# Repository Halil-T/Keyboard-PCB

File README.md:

# Keyboard-PCB
First Custom keyboard PCB

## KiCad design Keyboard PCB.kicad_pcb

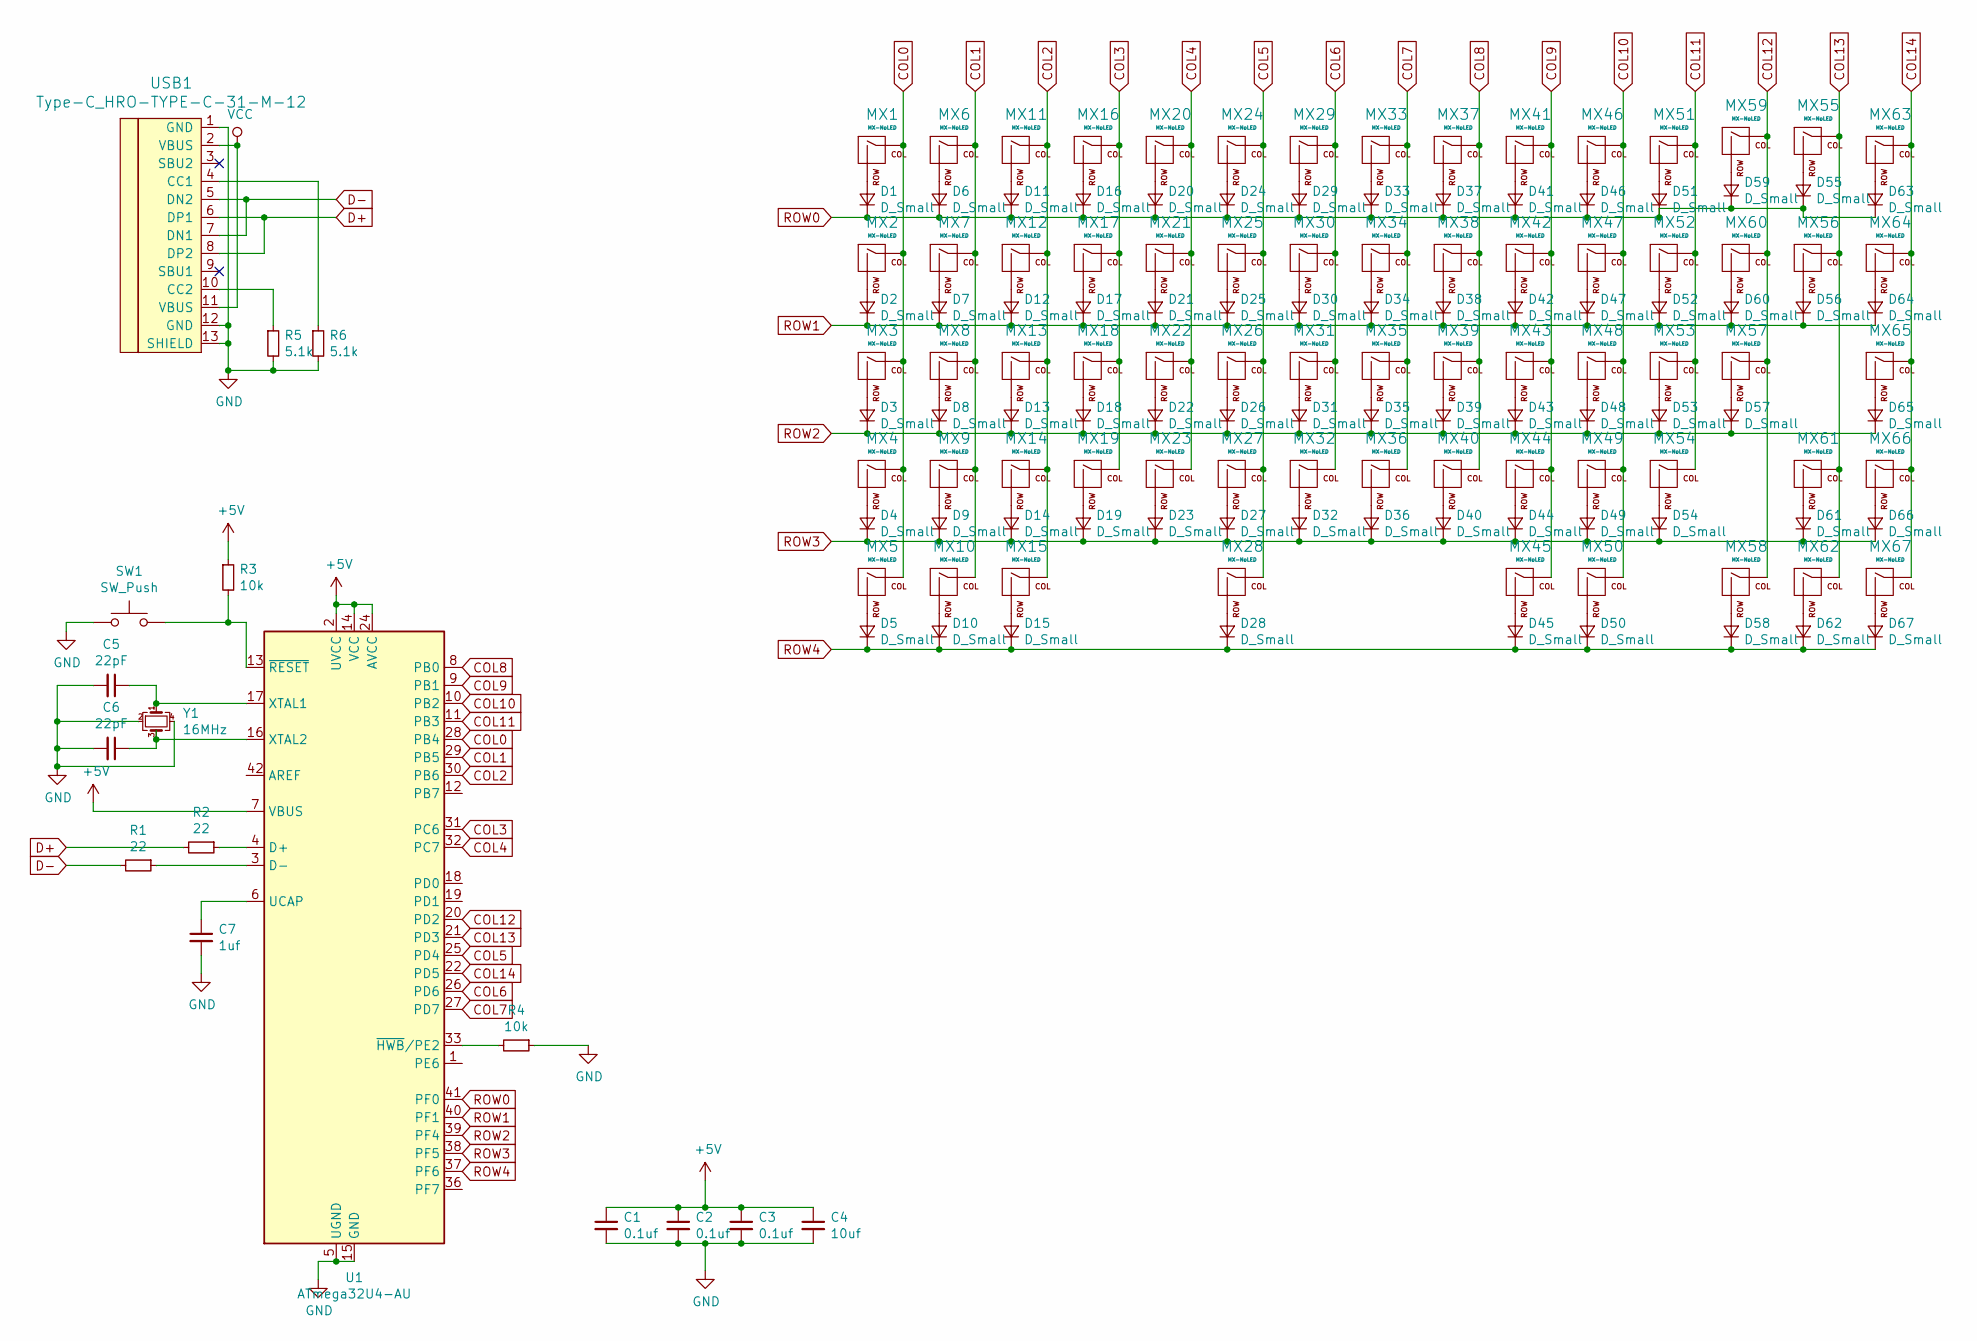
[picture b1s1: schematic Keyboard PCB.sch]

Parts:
C1, C2, C3: 0.1uf; C_0805_2012Metric_Pad1.15x1.40mm_HandSolder
C4: 10uf; C_0805_2012Metric_Pad1.15x1.40mm_HandSolder
C5, C6: 22pF; C_0805_2012Metric_Pad1.15x1.40mm_HandSolder
C7: 1uf; C_0805_2012Metric_Pad1.15x1.40mm_HandSolder
D1, D2, D3, D4, D5, D6, D7, D8, D9, D10, D11, D12, D13, D14, D15, D16, D17, D18, D19, D20, D21, D22, D23, D24, D25, D26, D27, D28, D29, D30, D31, D32, D33, D34, D35, D36, D37, D38, D39, D40, D41, D42, D43, D44, D45, D46, D47, D48, D49, D50, D51, D52, D53, D54, D55, D56, D57, D58, D59, D60, D61, D62, D63, D64, D65, D66, D67: D_Small; D_SOD-123
MX1, MX6, MX7, MX8, MX9, MX11, MX12, MX13, MX14, MX16, MX17, MX18, MX19, MX20, MX21, MX22, MX23, MX24, MX25, MX26, MX27, MX29, MX30, MX31, MX32, MX33, MX34, MX35, MX36, MX37, MX38, MX39, MX40, MX41, MX42, MX43, MX44, MX46, MX47, MX48, MX49, MX51, MX52, MX53, MX58, MX59, MX60, MX61, MX62, MX63, MX64, MX65, MX66, MX67: MX-NoLED; MX-1U-NoLED
MX2, MX56: MX-NoLED; MX-1.5U-NoLED
MX3, MX54: MX-NoLED; MX-1.75U-NoLED
MX4, MX57: MX-NoLED; MX-2.25U-NoLED
MX5, MX10, MX15, MX45, MX50: MX-NoLED; MX-1.25U-NoLED
MX28: MX-NoLED; MX-6.25U-ReversedStabilizers-NoLED
MX55: MX-NoLED; MX-2U-NoLED
R1, R2: 22; R_0805_2012Metric_Pad1.15x1.40mm_HandSolder
R3, R4: 10k; R_0805_2012Metric_Pad1.15x1.40mm_HandSolder
R5, R6: 5.1k; R_0805_2012Metric_Pad1.15x1.40mm_HandSolder
SW1: SW_Push; SKQG-1155865
U1: ATmega32U4-AU; TQFP-44_10x10mm_P0.8mm
USB1: Type-C_HRO-TYPE-C-31-M-12; HRO-TYPE-C-31-M-12-HandSoldering
Y1: 16MHz; Crystal_SMD_3225-4Pin_3.2x2.5mm_HandSoldering

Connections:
+5V: C1.1, C2.1, C3.1, C4.1, R3.1, U1.2 (UVCC), U1.7 (VBUS), U1.14 (VCC), U1.24 (AVCC), U1.34 (VCC), U1.44 (AVCC); also elsewhere on the board
COL0: MX1.1 (COL), MX2.1 (COL), MX3.1 (COL), MX4.1 (COL), MX5.1 (COL), U1.28 (PB4)
COL1: MX6.1 (COL), MX7.1 (COL), MX8.1 (COL), MX9.1 (COL), MX10.1 (COL), U1.29 (PB5)
COL2: MX11.1 (COL), MX12.1 (COL), MX13.1 (COL), MX14.1 (COL), MX15.1 (COL), U1.30 (PB6)
COL3: MX16.1 (COL), MX17.1 (COL), MX18.1 (COL), MX19.1 (COL), U1.31 (PC6)
COL4: MX20.1 (COL), MX21.1 (COL), MX22.1 (COL), MX23.1 (COL), U1.32 (PC7)
COL5: MX24.1 (COL), MX25.1 (COL), MX26.1 (COL), MX27.1 (COL), MX28.1 (COL), U1.25 (PD4)
COL6: MX29.1 (COL), MX30.1 (COL), MX31.1 (COL), MX32.1 (COL), U1.26 (PD6)
COL7: MX33.1 (COL), MX34.1 (COL), MX35.1 (COL), MX36.1 (COL), U1.27 (PD7)
COL8: MX37.1 (COL), MX38.1 (COL), MX39.1 (COL), MX40.1 (COL), U1.8 (PB0)
COL9: MX41.1 (COL), MX42.1 (COL), MX43.1 (COL), MX44.1 (COL), MX45.1 (COL), U1.9 (PB1)
COL10: MX46.1 (COL), MX47.1 (COL), MX48.1 (COL), MX49.1 (COL), MX50.1 (COL), U1.10 (PB2)
COL11: MX51.1 (COL), MX52.1 (COL), MX53.1 (COL), MX54.1 (COL), U1.11 (PB3)
COL12: MX57.1 (COL), MX58.1 (COL), MX59.1 (COL), MX60.1 (COL), U1.20 (PD2)
COL13: MX55.1 (COL), MX56.1 (COL), MX61.1 (COL), MX62.1 (COL), U1.21 (PD3)
COL14: MX63.1 (COL), MX64.1 (COL), MX65.1 (COL), MX66.1 (COL), MX67.1 (COL), U1.22 (PD5)
D+: R2.2, USB1.6 (DP1), USB1.8 (DP2)
D-: R1.2, USB1.5 (DN2), USB1.7 (DN1)
GND: C1.2, C2.2, C3.2, C4.2, C5.2, C6.2, C7.2, R4.1, R5.2, R6.2, SW1.1, U1.5 (UGND), U1.15 (GND), U1.23 (GND), U1.35 (GND), U1.43 (GND), USB1.1 (GND), USB1.12 (GND), USB1.13 (SHIELD), Y1.2, Y1.4
unnamed: C5.1, U1.17 (XTAL1), Y1.1
unnamed: C6.1, U1.16 (XTAL2), Y1.3
unnamed: C7.1, U1.6 (UCAP)
unnamed: D1.2 (A), MX1.2 (ROW)
unnamed: D2.2 (A), MX2.2 (ROW)
unnamed: D3.2 (A), MX3.2 (ROW)
unnamed: D4.2 (A), MX4.2 (ROW)
unnamed: D5.2 (A), MX5.2 (ROW)
unnamed: D6.2 (A), MX6.2 (ROW)
unnamed: D7.2 (A), MX7.2 (ROW)
unnamed: D8.2 (A), MX8.2 (ROW)
unnamed: D9.2 (A), MX9.2 (ROW)
unnamed: D10.2 (A), MX10.2 (ROW)
unnamed: D11.2 (A), MX11.2 (ROW)
unnamed: D12.2 (A), MX12.2 (ROW)
unnamed: D13.2 (A), MX13.2 (ROW)
unnamed: D14.2 (A), MX14.2 (ROW)
unnamed: D15.2 (A), MX15.2 (ROW)
unnamed: D16.2 (A), MX16.2 (ROW)
unnamed: D17.2 (A), MX17.2 (ROW)
unnamed: D18.2 (A), MX18.2 (ROW)
unnamed: D19.2 (A), MX19.2 (ROW)
unnamed: D20.2 (A), MX20.2 (ROW)
unnamed: D21.2 (A), MX21.2 (ROW)
unnamed: D22.2 (A), MX22.2 (ROW)
unnamed: D23.2 (A), MX23.2 (ROW)
unnamed: D24.2 (A), MX24.2 (ROW)
unnamed: D25.2 (A), MX25.2 (ROW)
unnamed: D26.2 (A), MX26.2 (ROW)
unnamed: D27.2 (A), MX27.2 (ROW)
unnamed: D28.2 (A), MX28.2 (ROW)
unnamed: D29.2 (A), MX29.2 (ROW)
unnamed: D30.2 (A), MX30.2 (ROW)
unnamed: D31.2 (A), MX31.2 (ROW)
unnamed: D32.2 (A), MX32.2 (ROW)
unnamed: D33.2 (A), MX33.2 (ROW)
unnamed: D34.2 (A), MX34.2 (ROW)
unnamed: D35.2 (A), MX35.2 (ROW)
unnamed: D36.2 (A), MX36.2 (ROW)
unnamed: D37.2 (A), MX37.2 (ROW)
unnamed: D38.2 (A), MX38.2 (ROW)
unnamed: D39.2 (A), MX39.2 (ROW)
unnamed: D40.2 (A), MX40.2 (ROW)
unnamed: D41.2 (A), MX41.2 (ROW)
unnamed: D42.2 (A), MX42.2 (ROW)
unnamed: D43.2 (A), MX43.2 (ROW)
unnamed: D44.2 (A), MX44.2 (ROW)
unnamed: D45.2 (A), MX45.2 (ROW)
unnamed: D46.2 (A), MX46.2 (ROW)
unnamed: D47.2 (A), MX47.2 (ROW)
unnamed: D48.2 (A), MX48.2 (ROW)
unnamed: D49.2 (A), MX49.2 (ROW)
unnamed: D50.2 (A), MX50.2 (ROW)
unnamed: D51.2 (A), MX51.2 (ROW)
unnamed: D52.2 (A), MX52.2 (ROW)
unnamed: D53.2 (A), MX53.2 (ROW)
unnamed: D54.2 (A), MX54.2 (ROW)
unnamed: D55.2 (A), MX55.2 (ROW)
unnamed: D56.2 (A), MX56.2 (ROW)
unnamed: D57.2 (A), MX57.2 (ROW)
unnamed: D58.2 (A), MX58.2 (ROW)
unnamed: D59.2 (A), MX59.2 (ROW)
unnamed: D60.2 (A), MX60.2 (ROW)
unnamed: D61.2 (A), MX61.2 (ROW)
unnamed: D62.2 (A), MX62.2 (ROW)
unnamed: D63.2 (A), MX63.2 (ROW)
unnamed: D64.2 (A), MX64.2 (ROW)
unnamed: D65.2 (A), MX65.2 (ROW)
unnamed: D66.2 (A), MX66.2 (ROW)
unnamed: D67.2 (A), MX67.2 (ROW)
unnamed: R1.1, U1.3 (D-)
unnamed: R2.1, U1.4 (D+)
unnamed: R3.2, SW1.2, U1.13 (~RESET)
unnamed: R4.2, U1.33 (~HWB~/PE2)
unnamed: R5.1, USB1.10 (CC2)
unnamed: R6.1, USB1.4 (CC1)
ROW0: D1.1 (K), D6.1 (K), D11.1 (K), D16.1 (K), D20.1 (K), D24.1 (K), D29.1 (K), D33.1 (K), D37.1 (K), D41.1 (K), D46.1 (K), D51.1 (K), D55.1 (K), D59.1 (K), D63.1 (K), U1.41 (PF0)
ROW1: D2.1 (K), D7.1 (K), D12.1 (K), D17.1 (K), D21.1 (K), D25.1 (K), D30.1 (K), D34.1 (K), D38.1 (K), D42.1 (K), D47.1 (K), D52.1 (K), D56.1 (K), D60.1 (K), D64.1 (K), U1.40 (PF1)
ROW2: D3.1 (K), D8.1 (K), D13.1 (K), D18.1 (K), D22.1 (K), D26.1 (K), D31.1 (K), D35.1 (K), D39.1 (K), D43.1 (K), D48.1 (K), D53.1 (K), D57.1 (K), D65.1 (K), U1.39 (PF4)
ROW3: D4.1 (K), D9.1 (K), D14.1 (K), D19.1 (K), D23.1 (K), D27.1 (K), D32.1 (K), D36.1 (K), D40.1 (K), D44.1 (K), D49.1 (K), D54.1 (K), D61.1 (K), D66.1 (K), U1.38 (PF5)
ROW4: D5.1 (K), D10.1 (K), D15.1 (K), D28.1 (K), D45.1 (K), D50.1 (K), D58.1 (K), D62.1 (K), D67.1 (K), U1.37 (PF6)
VCC: USB1.2 (VBUS), USB1.11 (VBUS); also elsewhere on the board

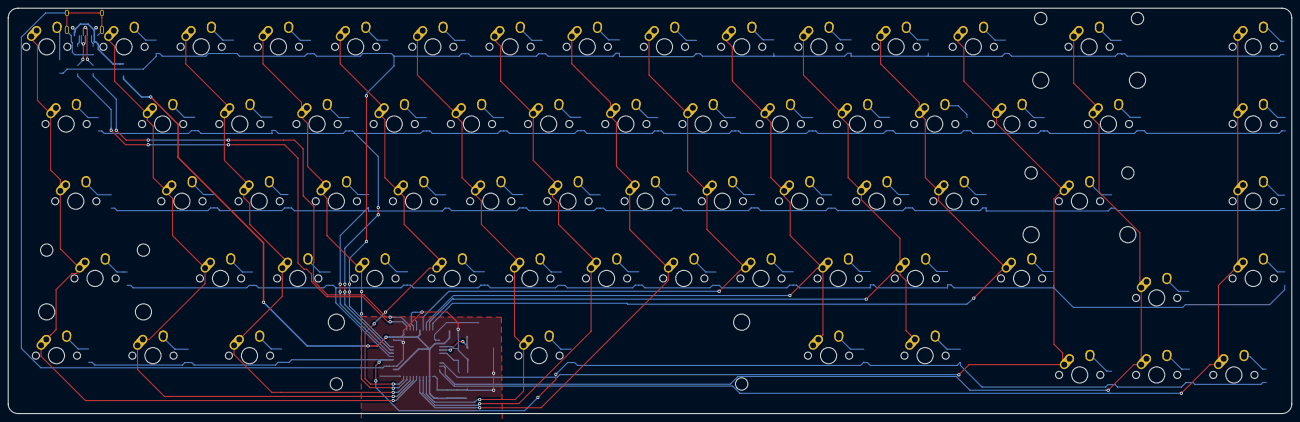
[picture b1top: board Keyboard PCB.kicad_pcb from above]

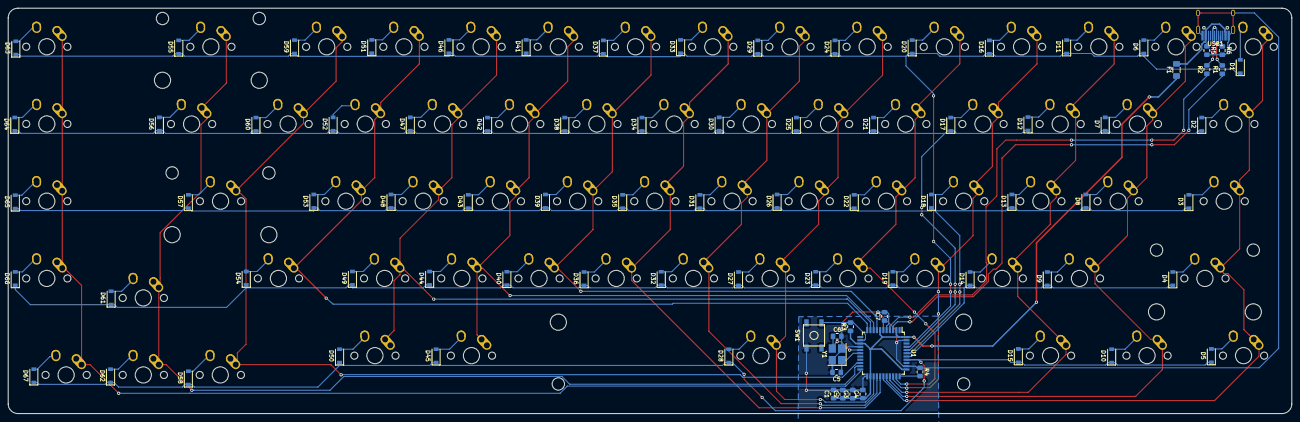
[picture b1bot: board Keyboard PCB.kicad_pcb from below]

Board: 2 copper layers, 316.7 x 100.0 mm, 152 parts (85 on the bottom side), 101 nets.

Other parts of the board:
F1: 500mA; Fuse_1206_3216Metric_Pad1.42x1.75mm_HandSolder

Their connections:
+5V: F1.1; also elsewhere on the board
VCC: F1.2; also elsewhere on the board

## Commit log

2020-02-11 Init Project
2020-02-11 Add submodules
2020-02-11 Add footprint libraries
2020-02-11 microchip setup
2020-02-11 Finalize Schematic
2020-02-13 Finishing assigning footprints
2020-02-14 PCB design part1
2020-02-15 PCB design
2020-02-16 column traces
2020-02-16 1st routing completion
2020-02-16 updating trace paths
2020-02-16 fixes
2020-02-17 FINAL
2020-02-17 USB C JST addon
2020-03-02 Final keyboard file extraction
